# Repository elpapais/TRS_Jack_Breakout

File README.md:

1/4" TRS Jack Breakout
========================================

[
*Part Name (SKU)*](URL for product on Sparkfun.com)

Breakout board for SparkFun [1/4" Stereo TRS jack](https://www.sparkfun.com/products/11144).  Makes jack easier to use with breadboards, and labels the connections to cut down on confusion about the normal connections.

Basic description of the part [The datasheet can be found here.](http://dlnmh9ip6v2uc.cloudfront.net/datasheets/Sensors/IMU/PS-MPU-9150A.pdf)

More information can be found on the Wiki for this repo. 

This part was created in Eagle v6.5.0. 

Repository Contents
-------------------

* **/Hardware** - All Eagle design files (.brd, .sch, .STL)
* **/Production** - Test bed files and production panel files

Product Versions
----------------
* [Part SKU](part URL)- Basic part and short description here
* [Retail part SKU] (retail URL)- Retail packaging of standard description here
* [Any other parts this repo covers](any other URLs) - Description of said parts

Version History
---------------
* [vExxFxxZxxHxxLxxSxx](URL for tag specific to this version) description 
* [vEyyFyyZyyHyyLyySyy](URL for tag specific to this version) description

License Information
-------------------
The hardware is released under [Creative Commons ShareAlike 4.0 International](https://creativecommons.org/licenses/by-sa/4.0/).
The code is beerware; if you see me (or any other SparkFun employee) at the local, and you've found our code helpful, please buy us a round!

Distributed as-is; no warranty is given.

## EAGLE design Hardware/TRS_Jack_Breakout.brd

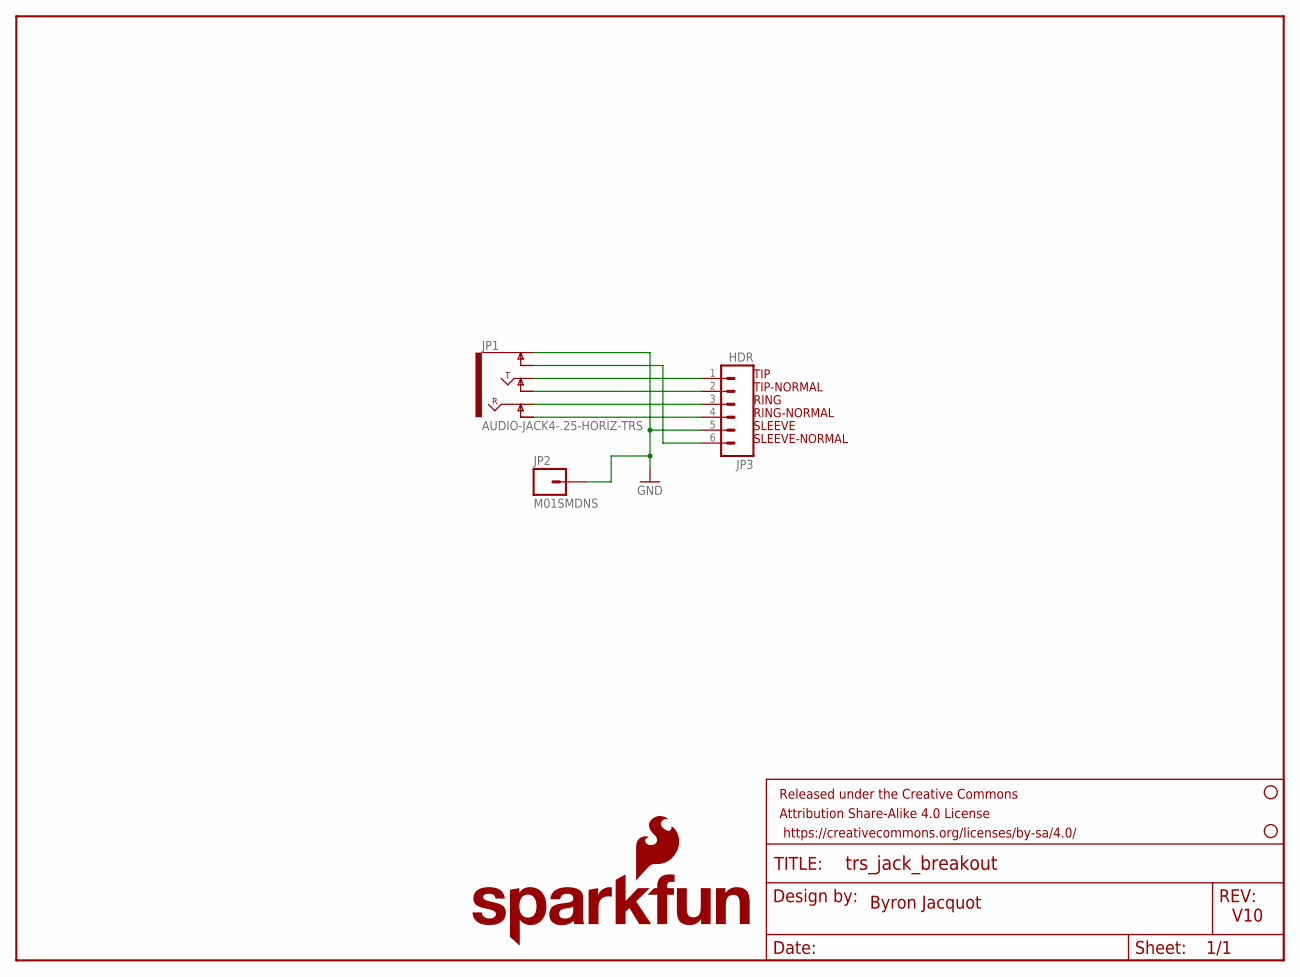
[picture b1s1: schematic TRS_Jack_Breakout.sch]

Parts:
FRAME1: FRAME-LETTER; CREATIVE_COMMONS
JP1: AUDIO-JACK4-.25-HORIZ-TRS; AUDIO-JACK-.25-INCH-HORIZ-PTH
JP2: M01SMDNS; 1X01NS
JP3: HDR; 1X06_NO_SILK
LOGO1: SFE_LOGO_NAME_FLAME.1_INCH; SFE_LOGO_NAME_FLAME_.1
STANDOFF1, STANDOFF2: STAND-OFF

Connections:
GND: JP1.SLEEVE (EARTH), JP2.1, JP3.5
unnamed: JP1.TIP, JP3.1
unnamed: JP1.TIP-NORM, JP3.2
unnamed: JP1.RING, JP3.3
unnamed: JP1.RING-NORM, JP3.4
unnamed: JP1.SLEEVE-NORM (EARTH-NORM), JP3.6

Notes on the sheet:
Byron Jacquot
V10
TIP
TIP-NORMAL
RING
RING-NORMAL
SLEEVE
SLEEVE-NORMAL

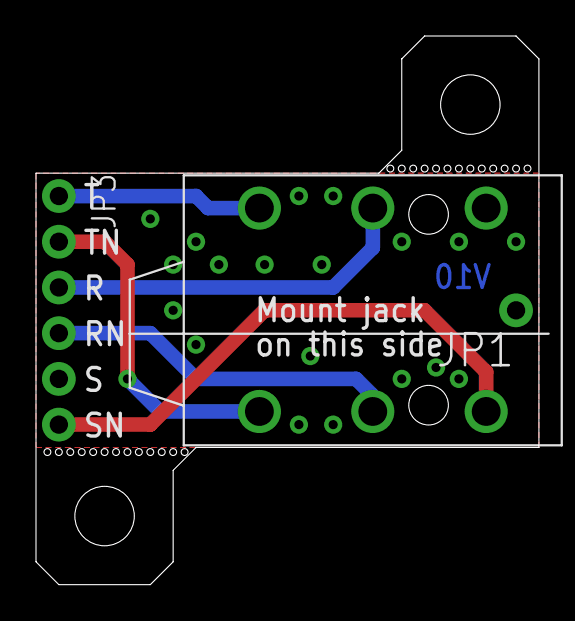
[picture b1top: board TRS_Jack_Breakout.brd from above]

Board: 2 copper layers, 27.9 x 30.5 mm, 7 parts (1 on the bottom side), 6 nets.

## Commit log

2014-06-24 Initial Commit
    Setting up repo boilerplate.
2014-06-24 Initial board & schem files
2014-06-30 Adding mounting holes on tabls, gnd pin
2014-07-14 Updating TRS jack footprint
    Drawing in datasheet isn't totally correct. The orientation bosses are
    not actually in line with the connections.
2014-08-05 Updating footprint based on protos
2014-08-05 Rethinking the rethink on the footprint.
    Got to looking closes at several jacks from stock - they're not very
    consistent, so bosses have been adapted to fit all of them.
2014-08-11 Updates after red review.
    Wider outline on dimension layer, added gear logo.
2014-09-09 Updating README with catalog links

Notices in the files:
parts and their libraries:
SparkFun-Aesthetics: Licensing: Creative Commons ShareAlike 4.0 International - https://creativecommons.org/licenses/by-sa/4.0
SparkFun-Aesthetics: Released under the Creative Commons Attribution Share-Alike 4.0 License
SparkFun-Aesthetics: Released under the Creative Commons
